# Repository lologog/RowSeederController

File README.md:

# DC Motor Controller for Row Seeder

## Project Description
This project focuses on the design and development of a modular DC motor controller system for a row seeder.
The system ensures precise control over seed dispensing and supports communication with external devices via CAN protocol.

The project consists of a main controller board an an extension board connected via 2.54mm pin sockets:
- **Main Controller Board**: Handles motor control, sensor readings and CAN communication protocol.
- **Extension Board**: Adds high-current switches and extra digital inputs for expanded functionality.

This modular approach allows future modifications for broader compatibility and functionality.

---

## Features
### Main Controller Board:
- **Microcontroller**: STM32L476RGT6 (low power, high-performance Cortex-M4).
- **DC Motor Control**: H-bridge driver with speed and direction regulation using PWM.
- **CAN Communication**: Communication interface enabled by an SN65HVD230 transceiver, operating with a default baud rate of 500 kbits/s.
- **Sensor Inputs**:
  - Analog inputs (12V) for angle sensors.
  - Encoder inputs (5V and 12V) for speed control.

### Extension Board:
- **Digital Input Expansion**: Additional pins for external sensors or signals.
- **High-current Switches**: Reliable control of external loads through robust switches.
- **Modular Connectivity**: Connects seamlessly to the main board via pin sockets.

---

## PCB Renderings
- **Main Controller Board**:

- **Extension Board**:

  *Extension PCB made by my friend :)*

---

## **Real-World Implementation**
Below are images of the actual hardware implementation:

- **Fully assembled main controller**:

- **Main controller connected with extension board**:

- **Whole controller packed in a cover with 4 connectors**:

---

## Results
- **PWM Motor Control**: Verified precise speed and direction control for the DC motor.
- **Sensor Readings**: Successfully processed analog inputs and encoders.
- **PID Algorithm**: Achieved stable motor speed with minimal overshoot and fast response.
  
  *Example motor angular velocity step response (fs = 10Hz)*
- **CAN Communication**: Reliable message transmission with external systems.
  
  *Sending analog reading of distance sensor via CAN bus*
  
---

## CAN Identifiers Documentation

The following table includes example CAN IDs and their corresponding actions. These IDs are meant as examples and should be adjusted to fit the needs of the target hardware and system.

| ID      | Function                | Parameters                     | Message Type    | Notes                                     |
|---------|-------------------------|--------------------------------|-----------------|-------------------------------------------|
| 0x01    | Ping                    | None                           | Response        | Sends a "ping" response                   |
| 0x02    | Turn LED ON             | None                           | Request         | Turns on the LED                          |
| 0x03    | Turn LED OFF            | None                           | Request         | Turns off the LED                         |
| 0x04    | Toggle LED state        | None                           | Request         | Toggles the LED state                     |
| 0x05    | Read distance sensor 1  | ADC channel                    | Request         | Reads analog measurement from channel 6   |
| 0x06    | Read distance sensor 2  | ADC channel                    | Request         | Reads analog measurement from channel 7   |
| 0x07    | Turn on/off switch 1    | 1 (ON), other (OFF)            | Request         | Controls power switch 1                   |
| 0x08    | Turn on/off switch 2    | 1 (ON), other (OFF)            | Request         | Controls power switch 2                   |
| 0x09    | Turn on/off switch 3    | 1 (ON), other (OFF)            | Request         | Controls power switch 3                   |
| 0x10    | Turn on/off switch 4    | 1 (ON), other (OFF)            | Request         | Controls power switch 4                   |
| 0x11    | Turn on/off switch 5    | 1 (ON), other (OFF)            | Request         | Controls power switch 5                   |
| 0x12    | Turn on/off switch 6    | 1 (ON), other (OFF)            | Request         | Controls power switch 6                   |
| 0x13    | Motor PID control       | RPM, direction                 | Request         | PID control for motor speed               |
| 0x14    | Stop motor              | None                           | Request         | Stops the motor                           |
| 0x15    | Motor percent control   | Percent, direction             | Request         | Controls motor using percentage duty cycle|

---

## Potential Improvements
- Support for a broader range of motors and sensors.
- Add more communication protocols and better diagnostic.
- Motor measurement for better motor control.
- Enhanced firmware for fault detection and recovery.
- Improved PID regulation using extrapolation between samples and implementation of angular speed control through current measurement.

## Author
- **Name**: Krzysztof Tomicki
- **Contact**: tomicki.krzysztof.pv@gmail.com

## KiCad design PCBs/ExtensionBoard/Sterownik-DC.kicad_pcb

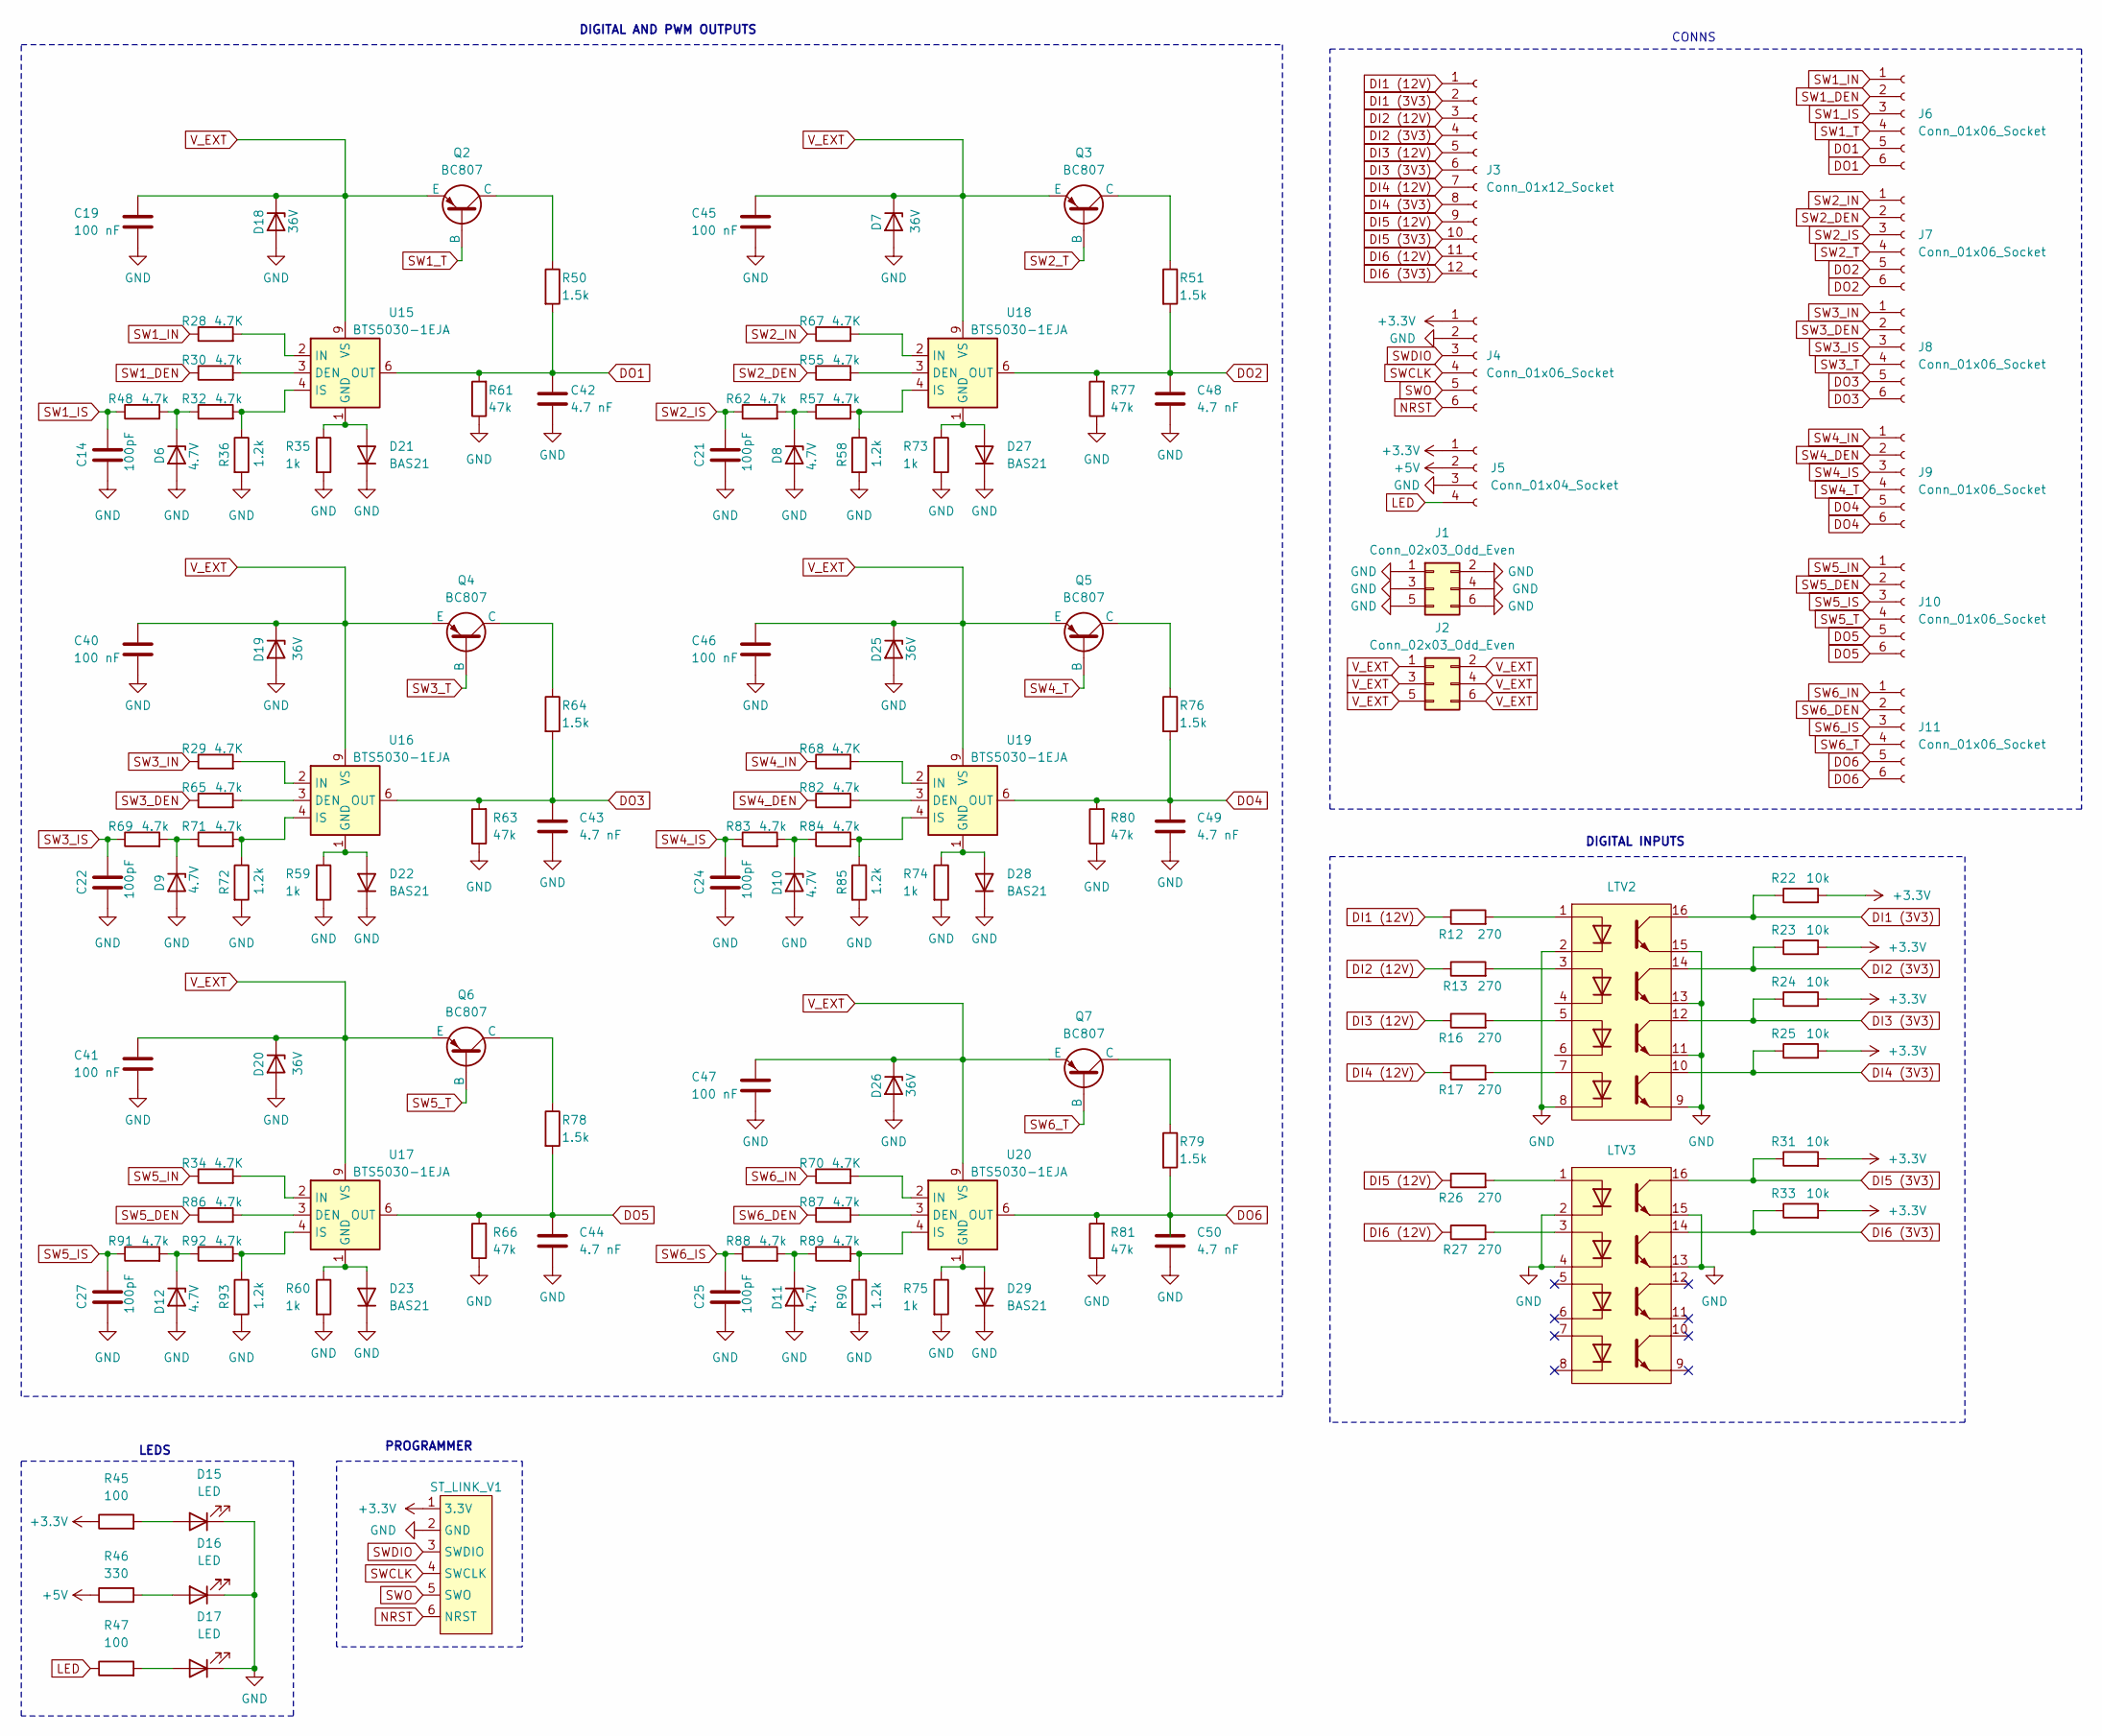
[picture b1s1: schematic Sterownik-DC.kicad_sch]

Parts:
C14, C21, C22, C24, C25, C27: 100pF; C_0805_2012Metric_Pad1.18x1.45mm_HandSolder
C19, C40, C41, C45, C46, C47: 100 nF; C_0805_2012Metric_Pad1.18x1.45mm_HandSolder
C42, C43, C44, C48, C49, C50: 4.7 nF; C_0805_2012Metric_Pad1.18x1.45mm_HandSolder
D6, D8, D9, D10, D11, D12: 4.7V; D_SOD-123
D7, D18, D19, D20, D25, D26: 36V; D_SOD-123
D15, D16, D17: LED; D_1206_3216Metric_Pad1.42x1.75mm_HandSolder
D21, D22, D23, D27, D28, D29: BAS21; SOT-23
J1, J2: Conn_02x03_Odd_Even; PinSocket_2x03_P2.54mm_Vertical
J3: Conn_01x12_Socket; PinSocket_2x06_P2.54mm_Vertical
J4, J6, J7, J8, J9, J10, J11: Conn_01x06_Socket; PinSocket_2x03_P2.54mm_Vertical
J5: Conn_01x04_Socket; PinSocket_2x02_P2.54mm_Vertical
LTV2, LTV3: DIP-16_W7.62mm
Q2, Q3, Q4, Q5, Q6, Q7: BC807; SOT-23-3
R12, R13, R16, R17, R26, R27: 270; R_1206_3216Metric_Pad1.30x1.75mm_HandSolder
R22, R23, R24, R25, R31, R33: 10k; R_0805_2012Metric_Pad1.20x1.40mm_HandSolder
R28, R29, R34, R67, R68, R70: 4.7K; R_0805_2012Metric_Pad1.20x1.40mm_HandSolder
R30, R32, R48, R55, R57, R62, R65, R69, R71, R82, R83, R84, R86, R87, R88, R89, R91, R92: 4.7k; R_0805_2012Metric_Pad1.20x1.40mm_HandSolder
R35, R59, R60, R73, R74, R75: 1k; R_0805_2012Metric_Pad1.20x1.40mm_HandSolder
R36, R58, R72, R85, R90, R93: 1.2k; R_0805_2012Metric_Pad1.20x1.40mm_HandSolder
R45, R47: 100; R_0805_2012Metric_Pad1.20x1.40mm_HandSolder
R46: 330; R_0805_2012Metric_Pad1.20x1.40mm_HandSolder
R50, R51, R64, R76, R78, R79: 1.5k; R_0805_2012Metric_Pad1.20x1.40mm_HandSolder
R61, R63, R66, R77, R80, R81: 47k; R_0805_2012Metric_Pad1.20x1.40mm_HandSolder
ST_LINK_V1: PinSocket_2x05_P2.54mm_Vertical
U15, U16, U17, U18, U19, U20: BTS5030-1EJA; Infineon_PG-DSO-8-43

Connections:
+3.3V: J4.1, J5.1, R22.2, R23.2, R24.2, R25.2, R31.2, R33.2, R45.1, ST_LINK_V1.1 (3.3V)
+5V: J5.2, R46.1
DI1 (3V3): J3.2, LTV2.16, R22.1
DI1 (12V): J3.1, R12.1
DI2 (3V3): J3.4, LTV2.14, R23.1
DI2 (12V): J3.3, R13.1
DI3 (3V3): J3.6, LTV2.12, R24.1
DI3 (12V): J3.5, R16.1
DI4 (3V3): J3.8, LTV2.10, R25.1
DI4 (12V): J3.7, R17.1
DI5 (3V3): J3.10, LTV3.16, R31.1
DI5 (12V): J3.9, R26.1
DI6 (3V3): J3.12, LTV3.14, R33.1
DI6 (12V): J3.11, R27.1
DO1: C42.1, J6.5, J6.6, R50.2, R61.2, U15.6 (OUT), U15.7 (OUT), U15.8 (OUT)
DO2: C48.1, J7.5, J7.6, R51.2, R77.2, U18.6 (OUT), U18.7 (OUT), U18.8 (OUT)
DO3: C43.1, J8.5, J8.6, R63.2, R64.2, U16.6 (OUT), U16.7 (OUT), U16.8 (OUT); also elsewhere on the board
DO4: C49.1, J9.5, J9.6, R76.2, R80.2, U19.6 (OUT), U19.7 (OUT), U19.8 (OUT)
DO5: C44.1, J10.5, J10.6, R66.2, R78.2, U17.6 (OUT), U17.7 (OUT), U17.8 (OUT)
DO6: C50.1, J11.5, J11.6, R79.2, R81.2, U20.6 (OUT), U20.7 (OUT), U20.8 (OUT)
GND: C14.1, C19.2, C21.1, C22.1, C24.1, C25.1, C27.1, C40.2, C41.2, C42.2, C43.2, C44.2, C45.2, C46.2, C47.2, C48.2, C49.2, C50.2, D6.2 (A), D7.2 (A), D8.2 (A), D9.2 (A), D10.2 (A), D12.2 (A), D15.1 (K), D16.1 (K), D17.1 (K), D18.2 (A), D19.2 (A), D20.2 (A), D21.3 (K), D22.3 (K), D23.3 (K), D25.2 (A), D26.2 (A), D27.3 (K), D28.3 (K), D29.3 (K), J1.1, J1.2, J1.3, J1.4, J1.5, J1.6, J4.2, J5.3, LTV2.2, LTV2.8, LTV2.9, LTV2.11, LTV2.13, LTV2.15, LTV3.2, LTV3.4, LTV3.13, LTV3.15, R35.2, R36.2, R58.2, R59.2, R60.2, R61.1, R63.1, R66.1, R72.2, R73.2, R74.2, R75.2, R77.1, R80.1, R81.1, R85.2, R90.2, R93.2, ST_LINK_V1.2 (GND); also elsewhere on the board
LED: J5.4, R47.1
NRST: J4.6, ST_LINK_V1.6 (NRST)
unnamed: D6.1 (K), R32.1, R48.2
unnamed: D8.1 (K), R57.1, R62.2
unnamed: D9.1 (K), R69.2, R71.1
unnamed: D10.1 (K), R83.2, R84.1
unnamed 27: D11.1 (K), R88.2, R89.1; also elsewhere on the board
unnamed: D12.1 (K), R91.2, R92.1
unnamed: D15.2 (A), R45.2
unnamed: D16.2 (A), R46.2
unnamed: D17.2 (A), R47.2
unnamed: D21.1 (A), R35.1, U15.1 (GND)
unnamed: D22.1 (A), R59.1, U16.1 (GND)
unnamed: D23.1 (A), R60.1, U17.1 (GND)
unnamed: D27.1 (A), R73.1, U18.1 (GND)
unnamed: D28.1 (A), R74.1, U19.1 (GND)
unnamed: D29.1 (A), R75.1, U20.1 (GND)
unnamed: LTV2.1, R12.2
unnamed: LTV2.3, R13.2
unnamed: LTV2.5, R16.2
unnamed: LTV2.7, R17.2
unnamed: LTV3.1, R26.2
unnamed: LTV3.3, R27.2
unnamed: Q2.1 (C), R50.1
unnamed: Q3.1 (C), R51.1
unnamed 46: Q4.1 (C), R64.1; also elsewhere on the board
unnamed: Q5.1 (C), R76.1
unnamed: Q6.1 (C), R78.1
unnamed: Q7.1 (C), R79.1
unnamed: R30.2, U15.3 (DEN)
unnamed: R28.2, U15.2 (IN)
unnamed: R32.2, R36.1, U15.4 (IS)
unnamed: R65.2, U16.3 (DEN)
unnamed: R29.2, U16.2 (IN)
unnamed: R71.2, R72.1, U16.4 (IS)
unnamed: R86.2, U17.3 (DEN)
unnamed: R34.2, U17.2 (IN)
unnamed: R92.2, R93.1, U17.4 (IS)
unnamed: R55.2, U18.3 (DEN)
unnamed: R67.2, U18.2 (IN)
unnamed: R57.2, R58.1, U18.4 (IS)
unnamed: R82.2, U19.3 (DEN)
unnamed: R68.2, U19.2 (IN)
unnamed: R84.2, R85.1, U19.4 (IS)
unnamed: R87.2, U20.3 (DEN)
unnamed: R70.2, U20.2 (IN)
unnamed: R89.2, R90.1, U20.4 (IS)
SW1_DEN: J6.2, R30.1
SW1_IN: J6.1, R28.1
SW1_IS: C14.2, J6.3, R48.1
SW1_T: J6.4, Q2.2 (B)
SW2_DEN: J7.2, R55.1
SW2_IN: J7.1, R67.1
SW2_IS: C21.2, J7.3, R62.1
SW2_T: J7.4, Q3.2 (B)
SW3_DEN: J8.2, R65.1
SW3_IN: J8.1, R29.1
SW3_IS: C22.2, J8.3, R69.1
SW3_T: J8.4, Q4.2 (B)
SW4_DEN: J9.2, R82.1
SW4_IN: J9.1, R68.1
SW4_IS: C24.2, J9.3, R83.1
SW4_T: J9.4, Q5.2 (B)
SW5_DEN: J10.2, R86.1
SW5_IN: J10.1, R34.1
SW5_IS: C27.2, J10.3, R91.1
SW5_T: J10.4, Q6.2 (B)
SW6_DEN: J11.2, R87.1
SW6_IN: J11.1, R70.1
SW6_IS: C25.2, J11.3, R88.1
SW6_T: J11.4, Q7.2 (B)
SWCLK: J4.4, ST_LINK_V1.4 (SWCLK)
SWDIO: J4.3, ST_LINK_V1.3 (SWDIO)
SWO: J4.5, ST_LINK_V1.5 (SWO)
V_EXT: C19.1, C40.1, C41.1, C45.1, C46.1, C47.1, D7.1 (K), D18.1 (K), D19.1 (K), D20.1 (K), D25.1 (K), D26.1 (K), J2.1, J2.2, J2.3, J2.4, J2.5, J2.6, Q2.3 (E), Q3.3 (E), Q4.3 (E), Q5.3 (E), Q6.3 (E), Q7.3 (E), U15.9 (VS), U16.9 (VS), U17.9 (VS), U18.9 (VS), U19.9 (VS), U20.9 (VS)

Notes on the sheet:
CONNS
DIGITAL INPUTS
DIGITAL AND PWM OUTPUTS
LEDS
PROGRAMMER

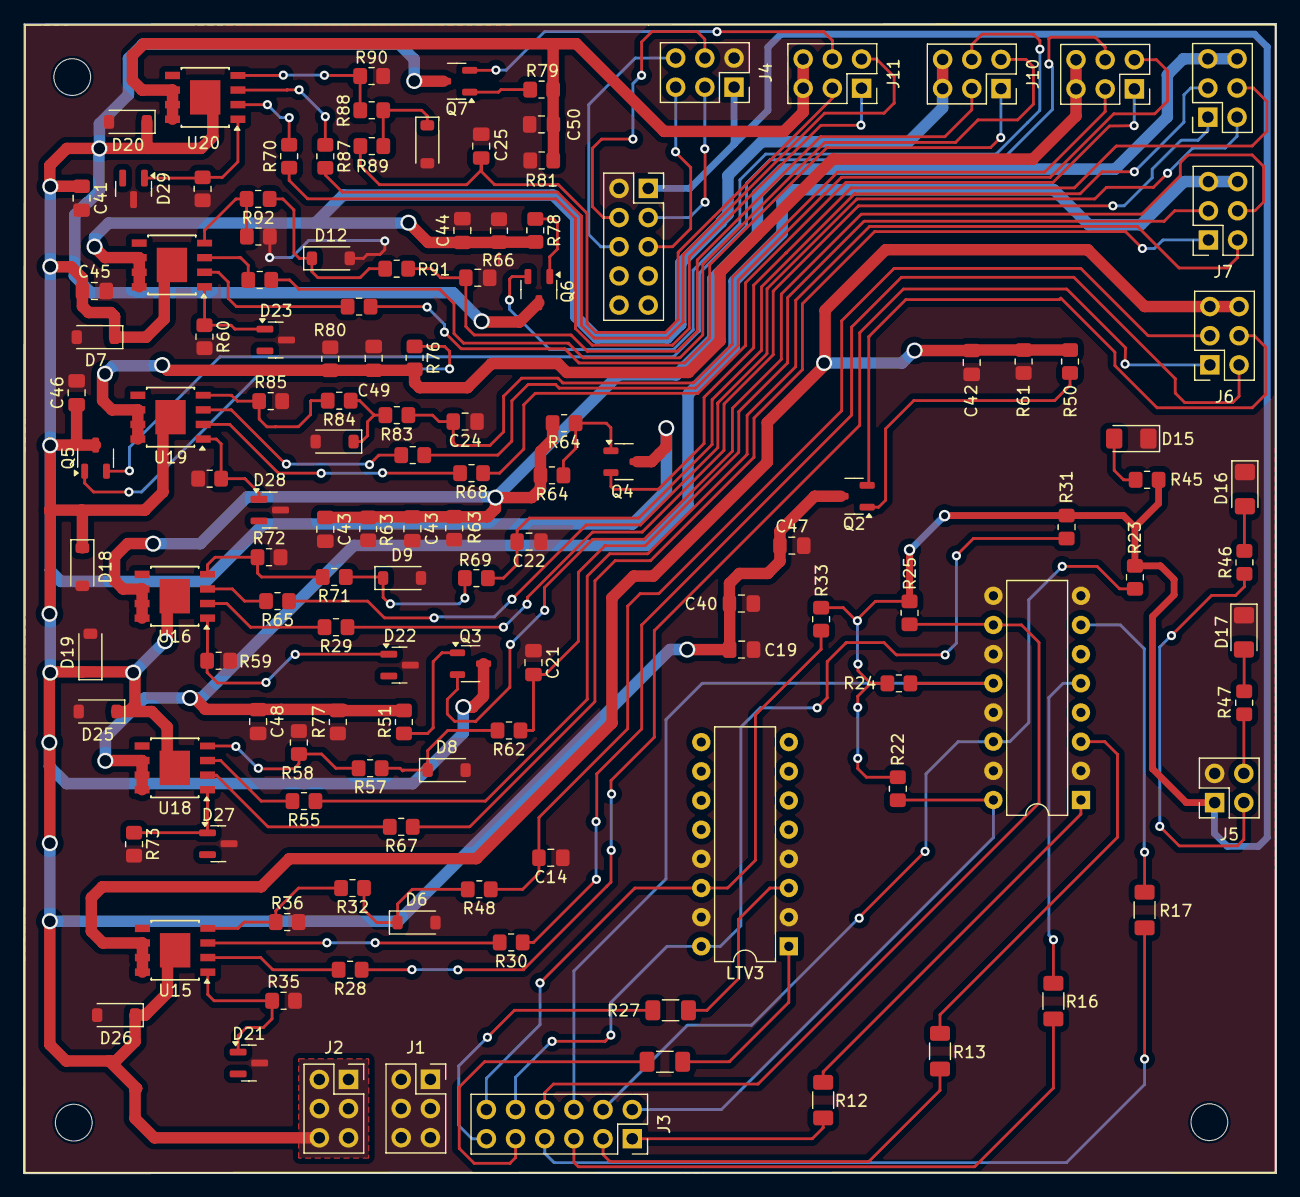
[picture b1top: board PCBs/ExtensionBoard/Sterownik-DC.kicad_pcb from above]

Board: 2 copper layers, 109.1 x 100.1 mm, 131 parts (0 on the bottom side), 96 nets.

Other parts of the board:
C25#2: 4.7V; D_SOD-123
C43#2: 4.7 nF; C_0805_2012Metric_Pad1.18x1.45mm_HandSolder
R63#2: 47k; R_0805_2012Metric_Pad1.20x1.40mm_HandSolder
R64#2: 1.5k; R_0805_2012Metric_Pad1.20x1.40mm_HandSolder

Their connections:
DO3: C43#2.1, R63#2.2, R64#2.2; also elsewhere on the board
GND: C25#2.2 (A), C43#2.2, R63#2.1; also elsewhere on the board
unnamed 27: C25#2.1 (K); also elsewhere on the board
unnamed 46: R64#2.1; also elsewhere on the board

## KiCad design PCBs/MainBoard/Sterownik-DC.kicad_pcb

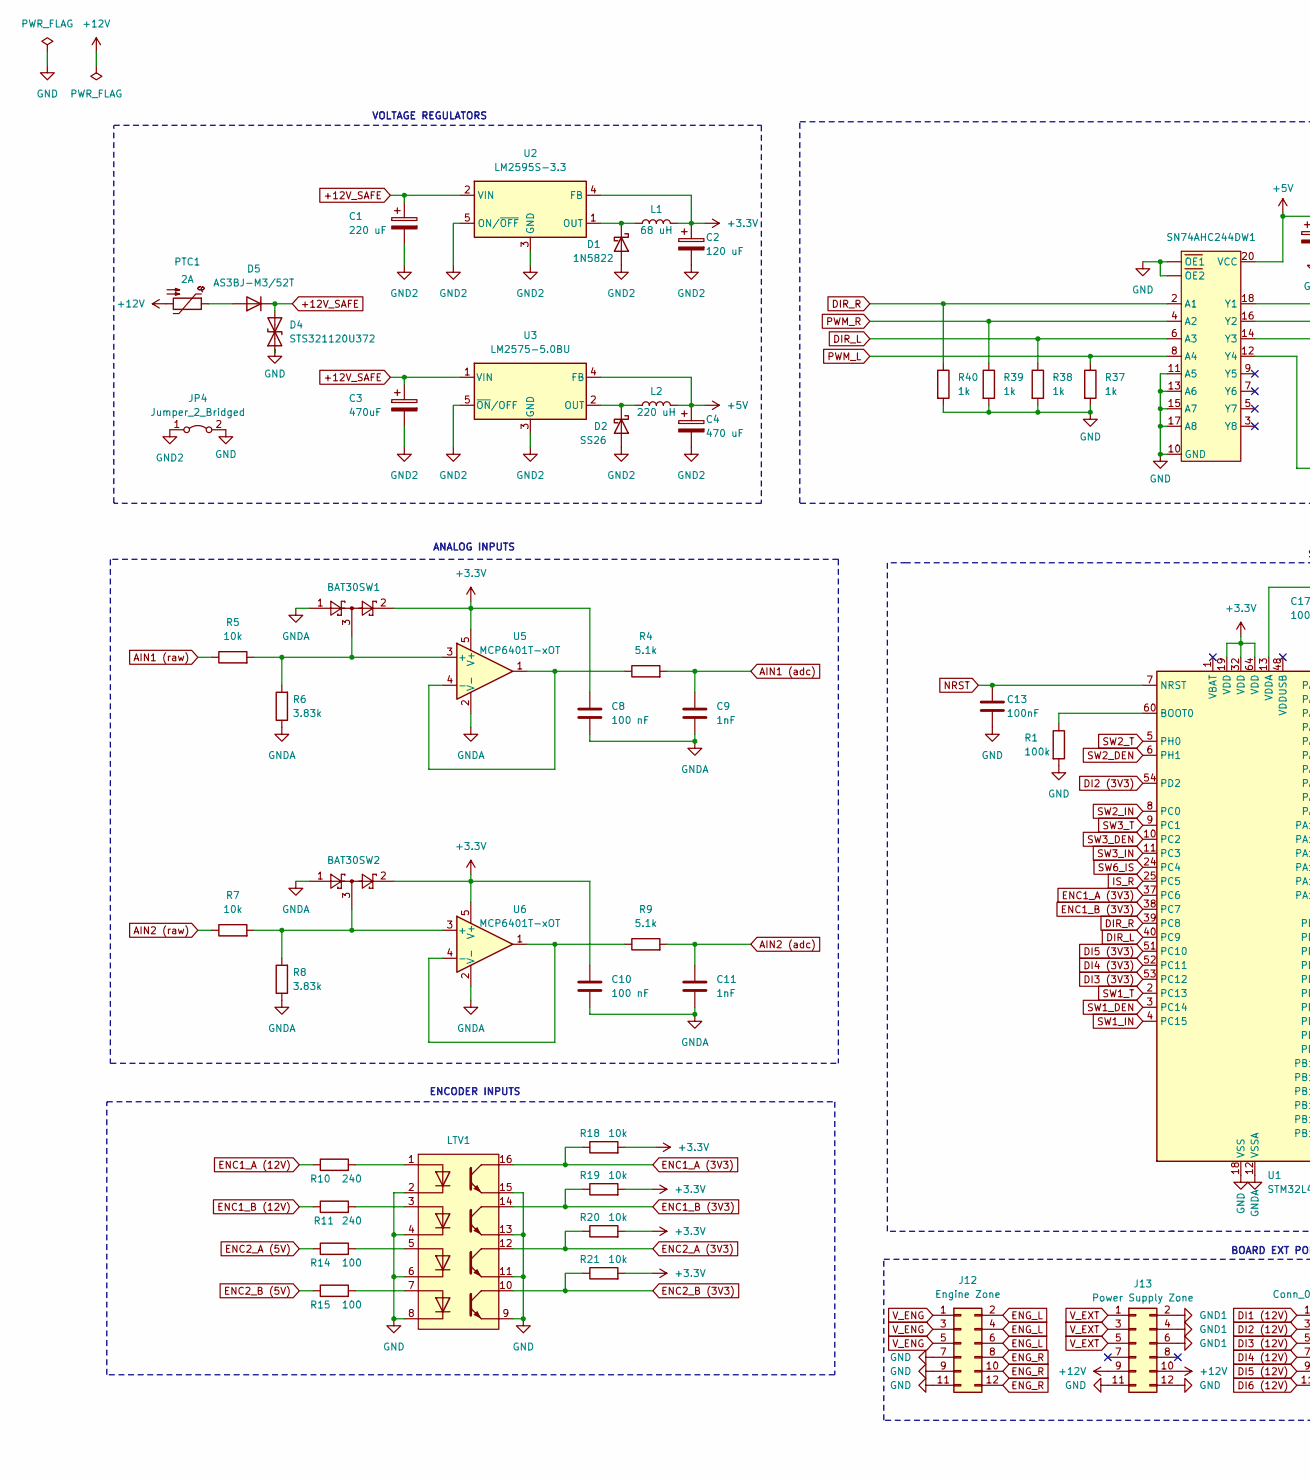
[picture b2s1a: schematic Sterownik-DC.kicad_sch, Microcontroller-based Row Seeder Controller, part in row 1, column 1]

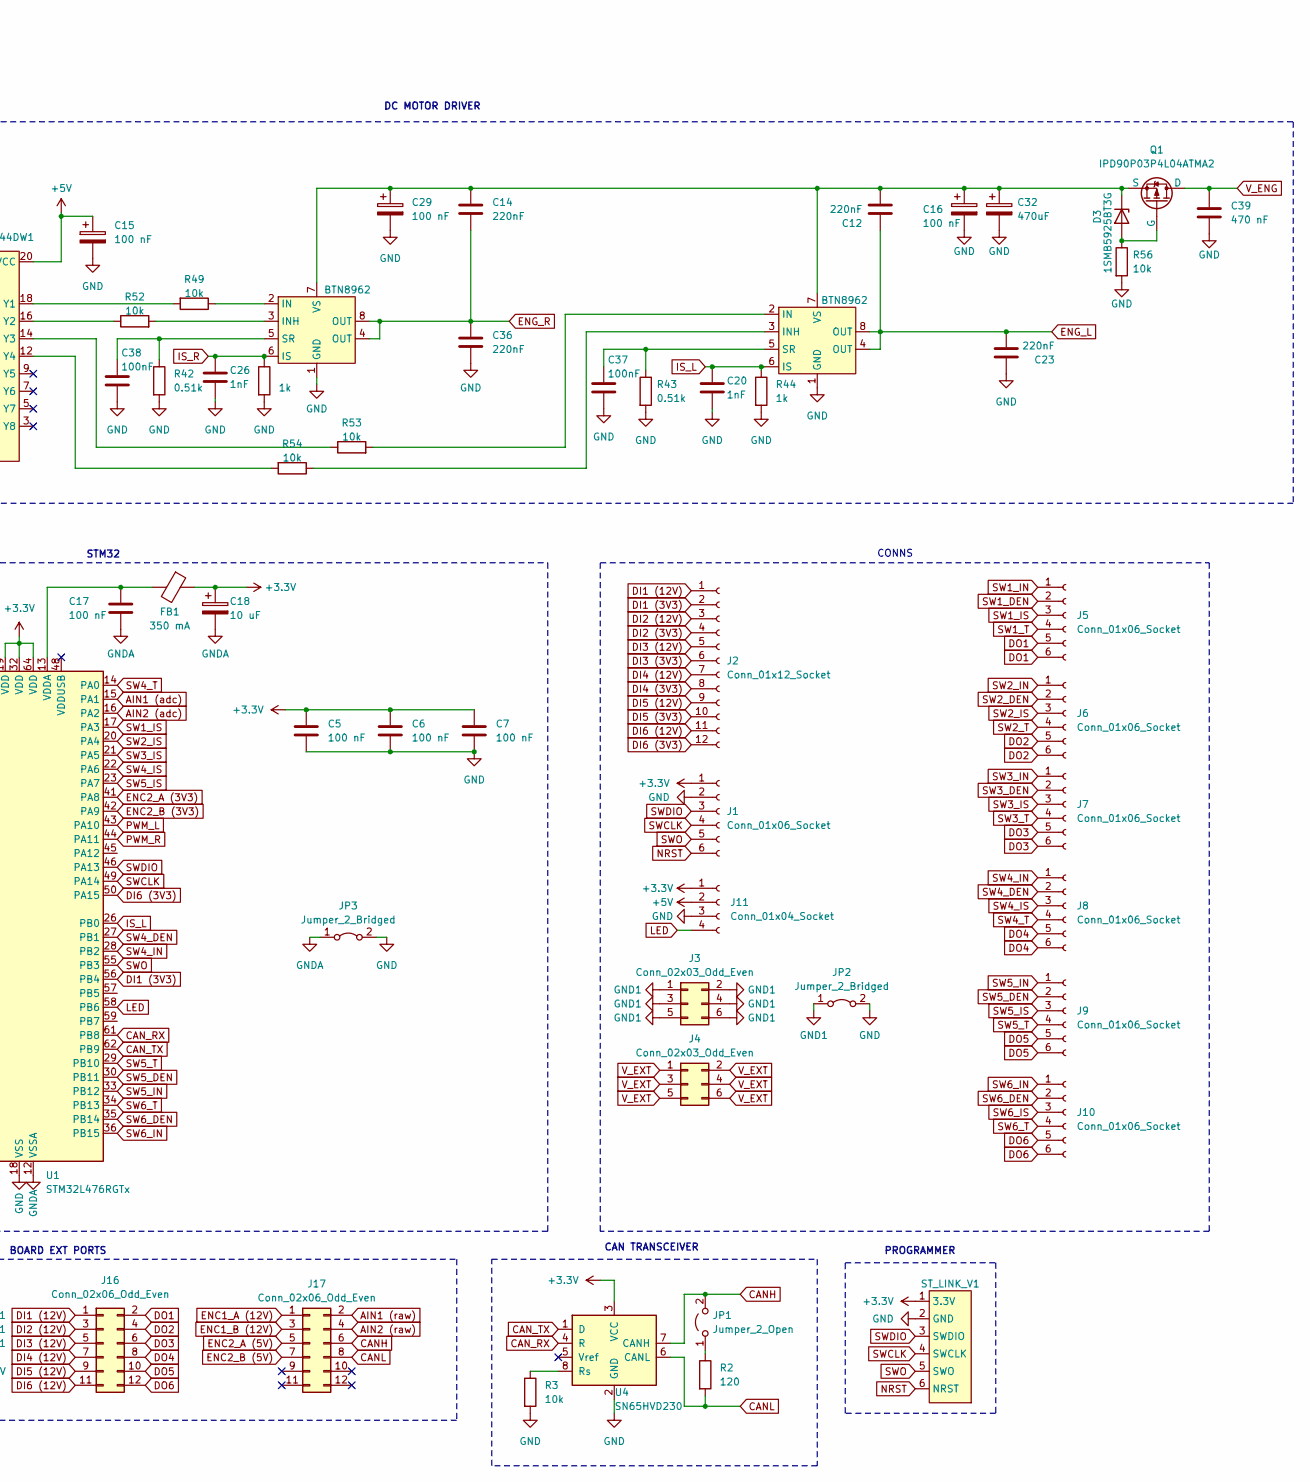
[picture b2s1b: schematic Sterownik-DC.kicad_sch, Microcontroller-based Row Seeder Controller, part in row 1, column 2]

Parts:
BAT30SW1, BAT30SW2: SOT-323_SC-70
C1: 220 uF; CP_Radial_D8.0mm_P3.50mm
C2: 120 uF; CP_Radial_D8.0mm_P3.50mm
C3, C32: 470uF; CP_Radial_D10.0mm_P5.00mm
C4: 470 uF; CP_Radial_D10.0mm_P5.00mm
C5, C6, C7, C8, C10, C15, C16, C17, C29: 100 nF; C_0805_2012Metric_Pad1.18x1.45mm_HandSolder
C9, C11, C20, C26: 1nF; C_0805_2012Metric_Pad1.18x1.45mm_HandSolder
C12, C14, C23, C36: 220nF; C_0805_2012Metric_Pad1.18x1.45mm_HandSolder
C13, C37, C38: 100nF; C_0805_2012Metric_Pad1.18x1.45mm_HandSolder
C18: 10 uF; C_0805_2012Metric_Pad1.18x1.45mm_HandSolder
C39: 470 nF; C_0805_2012Metric_Pad1.18x1.45mm_HandSolder
D1: 1N5822; D_SMA_Handsoldering
D2: SS26; Zener_diode_DO-214AA
D3: 1SMB5925BT3G; 1SMB5913BT3
D4: STS321120U372; D_SOD-323_HandSoldering
D5: AS3BJ-M3/52T; AS3BJ-M3-52T
FB1: 350 mA; L_1206_3216Metric_Pad1.22x1.90mm_HandSolder
J1, J5, J6, J7, J8, J9, J10: Conn_01x06_Socket; PinSocket_2x03_P2.54mm_Vertical
J2: Conn_01x12_Socket; PinSocket_2x06_P2.54mm_Vertical
J3, J4: Conn_02x03_Odd_Even; PinSocket_2x03_P2.54mm_Vertical
J11: Conn_01x04_Socket; PinSocket_2x02_P2.54mm_Vertical
J12: Engine Zone; BIG_CONN
J13: Power Supply Zone; BIG_CONN
J16, J17: Conn_02x06_Odd_Even; BIG_CONN
JP1: Jumper_2_Open; PinHeader_1x02_P2.54mm_Vertical
JP2, JP3, JP4: Jumper_2_Bridged; SolderJumper-2_P1.3mm_Bridged2Bar_Pad1.0x1.5mm
L1: 68 uH; SRR1280
L2: 220 uH; MSS1246T
LTV1: DIP-16_W7.62mm
PTC1: 2A; 0ZCF Series
Q1: IPD90P03P4L04ATMA2; TO-252-3_TabPin2
R1: 100k; R_0805_2012Metric_Pad1.20x1.40mm_HandSolder
R2: 120; R_0805_2012Metric_Pad1.20x1.40mm_HandSolder
R3, R5, R7, R18, R19, R20, R21, R49, R52, R53, R54, R56: 10k; R_0805_2012Metric_Pad1.20x1.40mm_HandSolder
R4, R9: 5.1k; R_0805_2012Metric_Pad1.20x1.40mm_HandSolder
R6, R8: 3.83k; R_0805_2012Metric_Pad1.20x1.40mm_HandSolder
R10, R11: 240; R_2512_6332Metric_Pad1.40x3.35mm_HandSolder
R14, R15: 100; R_0805_2012Metric_Pad1.20x1.40mm_HandSolder
R37, R38, R39, R40, R41, R44: 1k; R_0805_2012Metric_Pad1.20x1.40mm_HandSolder
R42, R43: 0.51k; R_0805_2012Metric_Pad1.20x1.40mm_HandSolder
SN74AHC244DW1: SOIC-20W_7.5x12.8mm_P1.27mm
ST_LINK_V1: PinSocket_2x05_P2.54mm_Vertical
U1: STM32L476RGTx; LQFP-64_10x10mm_P0.5mm
U2: LM2595S-3.3; TO-263-5_TabPin3
U3: LM2575-5.0BU; TO-263-5_TabPin3
U4: SN65HVD230; SOIC-8_3.9x4.9mm_P1.27mm
U5, U6: MCP6401T-xOT; SOT-23-5
U8, U9: BTN8962; TO-263-7_TabPin8

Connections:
+3.3V: BAT30SW1.2, BAT30SW2.2, C2.1, C5.1, C6.1, C7.1, C8.1, C10.1, C18.1, FB1.1, J1.1, J11.1, L1.2, R18.2, R19.2, R20.2, R21.2, ST_LINK_V1.1 (3.3V), U1.19 (VDD), U1.32 (VDD), U1.64 (VDD), U2.4 (FB), U4.3 (VCC), U5.5 (V+), U6.5 (V+)
+5V: C4.1, C15.1, J11.2, L2.2, SN74AHC244DW1.20 (VCC), U3.4 (FB)
+12V: J13.9, J13.10, PTC1.2
+12V_SAFE: C1.1, C3.1, D4.2 (A2), D5.1 (K), U2.2 (VIN), U3.1 (VIN)
AIN1 (adc): C9.1, R4.2, U1.15 (PA1)
AIN1 (raw): J17.2, R5.1
AIN2 (adc): C11.1, R9.2, U1.16 (PA2)
AIN2 (raw): J17.4, R7.1
CANH: J17.6, JP1.2 (B), U4.7 (CANH)
CANL: J17.8, R2.2, U4.6 (CANL)
CAN_RX: U1.61 (PB8), U4.4 (R)
CAN_TX: U1.62 (PB9), U4.1 (D)
DI1 (3V3): J2.2, U1.56 (PB4)
DI1 (12V): J2.1, J16.1
DI2 (3V3): J2.4, U1.54 (PD2)
DI2 (12V): J2.3, J16.3
DI3 (3V3): J2.6, U1.53 (PC12)
DI3 (12V): J2.5, J16.5
DI4 (3V3): J2.8, U1.52 (PC11)
DI4 (12V): J2.7, J16.7
DI5 (3V3): J2.10, U1.51 (PC10)
DI5 (12V): J2.9, J16.9
DI6 (3V3): J2.12, U1.50 (PA15)
DI6 (12V): J2.11, J16.11
DIR_L: R38.1, SN74AHC244DW1.6 (A3), U1.40 (PC9)
DIR_R: R40.1, SN74AHC244DW1.2 (A1), U1.39 (PC8)
DO1: J5.5, J5.6, J16.2
DO2: J6.5, J6.6, J16.4
DO3: J7.5, J7.6, J16.6
DO4: J8.5, J8.6, J16.8
DO5: J9.5, J9.6, J16.10
DO6: J10.5, J10.6, J16.12
ENC1_A (3V3): LTV1.16, R18.1, U1.37 (PC6)
ENC1_A (12V): J17.1, R10.1
ENC1_B (3V3): LTV1.14, R19.1, U1.38 (PC7)
ENC1_B (12V): J17.3, R11.1
ENC2_A (3V3): LTV1.12, R20.1, U1.41 (PA8)
ENC2_A (5V): J17.5, R14.1
ENC2_B (3V3): LTV1.10, R21.1, U1.42 (PA9)
ENC2_B (5V): J17.7, R15.1
ENG_L: C12.1, C23.2, J12.2, J12.4, J12.6, U9.4 (OUT), U9.8 (OUT)
ENG_R: C14.2, C36.1, J12.8, J12.10, J12.12, U8.4 (OUT), U8.8 (OUT)
GND: C5.2, C6.2, C7.2, C13.2, C15.2, C16.2, C20.2, C23.1, C26.2, C29.2, C32.2, C36.2, C37.2, C38.2, C39.2, D4.1 (A1), J1.2, J11.3, J12.7, J12.9, J12.11, J13.11, J13.12, JP2.2 (B), JP3.2 (B), JP4.2 (B), LTV1.2, LTV1.4, LTV1.6, LTV1.8, LTV1.9, LTV1.11, LTV1.13, LTV1.15, R1.2, R3.2, R37.2, R38.2, R39.2, R40.2, R41.2, R42.2, R43.2, R44.2, R56.2, SN74AHC244DW1. (OE1), SN74AHC244DW1.1 (OE1), SN74AHC244DW1.10 (GND), SN74AHC244DW1.11 (A5), SN74AHC244DW1.13 (A6), SN74AHC244DW1.15 (A7), SN74AHC244DW1.17 (A8), SN74AHC244DW1.19 (OE2), ST_LINK_V1.2 (GND), U1.18 (VSS), U1.31 (VSS), U1.47 (VSS), U1.63 (VSS), U4.2 (GND), U8.1 (GND), U9.1 (GND)
GND1: J3.1, J3.2, J3.3, J3.4, J3.5, J3.6, J13.2, J13.4, J13.6, JP2.1 (A)
GND2: C1.2, C2.2, C3.2, C4.2, D1.2 (A), D2.2 (A), JP4.1 (A), U2.3 (GND), U2.5 (ON/~OFF), U3.3 (GND), U3.5 (~ON/OFF)
GNDA: BAT30SW1.1, BAT30SW2.1, C8.2, C9.2, C10.2, C11.2, C17.2, C18.2, JP3.1 (A), R6.1, R8.1, U1.12 (VSSA), U5.2 (V-), U6.2 (V-)
IS_L: C20.1, R44.1, U1.26 (PB0), U9.6 (IS)
IS_R: C26.1, R41.1, U1.25 (PC5), U8.6 (IS)
LED: J11.4, U1.58 (PB6)
NRST: C13.1, J1.6, ST_LINK_V1.6 (NRST), U1.7 (NRST)
unnamed: D1.1 (K), L1.1, U2.1 (OUT)
unnamed: D2.1 (K), L2.1, U3.2 (OUT)
unnamed: D3.2 (A), Q1.1 (G), R56.1
unnamed: C12.2, C14.1, C16.1, C29.1, C32.1, D3.1 (K), Q1.3 (S), U8.7 (VS), U9.7 (VS)
unnamed: D5.2 (A), PTC1.1
unnamed: JP1.1 (A), R2.1
unnamed: LTV1.1, R10.2
unnamed: LTV1.3, R11.2
unnamed: LTV1.5, R14.2
unnamed: LTV1.7, R15.2
unnamed: R49.2, SN74AHC244DW1.18 (Y1)
unnamed: R52.1, SN74AHC244DW1.16 (Y2)
unnamed: R53.1, SN74AHC244DW1.14 (Y3)
unnamed: R54.2, SN74AHC244DW1.12 (Y4)
unnamed: R1.1, U1.60 (BOOT0)
unnamed: C17.1, FB1.2, U1.13 (VDDA)
unnamed: R3.1, U4.8 (Rs)
unnamed: BAT30SW1.3, R5.2, R6.2, U5.3 (+)
unnamed: R4.1, U5.1, U5.4 (-)
unnamed: BAT30SW2.3, R7.2, R8.2, U6.3 (+)
unnamed: R9.1, U6.1, U6.4 (-)
unnamed: R49.1, U8.2 (IN)
unnamed: R52.2, U8.3 (INH)
unnamed: C38.1, R42.1, U8.5 (SR)
unnamed: R53.2, U9.2 (IN)
unnamed: R54.1, U9.3 (INH)
unnamed: C37.1, R43.1, U9.5 (SR)
PWM_L: R37.1, SN74AHC244DW1.8 (A4), U1.43 (PA10)
PWM_R: R39.1, SN74AHC244DW1.4 (A2), U1.44 (PA11)
SW1_DEN: J5.2, U1.3 (PC14)
SW1_IN: J5.1, U1.4 (PC15)
SW1_IS: J5.3, U1.17 (PA3)
SW1_T: J5.4, U1.2 (PC13)
SW2_DEN: J6.2, U1.6 (PH1)
SW2_IN: J6.1, U1.8 (PC0)
SW2_IS: J6.3, U1.20 (PA4)
SW2_T: J6.4, U1.5 (PH0)
SW3_DEN: J7.2, U1.10 (PC2)
SW3_IN: J7.1, U1.11 (PC3)
SW3_IS: J7.3, U1.21 (PA5)
SW3_T: J7.4, U1.9 (PC1)
SW4_DEN: J8.2, U1.27 (PB1)
SW4_IN: J8.1, U1.28 (PB2)
SW4_IS: J8.3, U1.22 (PA6)
SW4_T: J8.4, U1.14 (PA0)
SW5_DEN: J9.2, U1.30 (PB11)
SW5_IN: J9.1, U1.33 (PB12)
SW5_IS: J9.3, U1.23 (PA7)
SW5_T: J9.4, U1.29 (PB10)
SW6_DEN: J10.2, U1.35 (PB14)
SW6_IN: J10.1, U1.36 (PB15)
SW6_IS: J10.3, U1.24 (PC4)
SW6_T: J10.4, U1.34 (PB13)
SWCLK: J1.4, ST_LINK_V1.4 (SWCLK), U1.49 (PA14)
SWDIO: J1.3, ST_LINK_V1.3 (SWDIO), U1.46 (PA13)
SWO: J1.5, ST_LINK_V1.5 (SWO), U1.55 (PB3)
V_ENG: C39.1, J12.1, J12.3, J12.5, Q1.2 (D)
V_EXT: J4.1, J4.2, J4.3, J4.4, J4.5, J4.6, J13.1, J13.3, J13.5

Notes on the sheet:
DC MOTOR DRIVER
CONNS
PROGRAMMER
CAN TRANSCEIVER
ANALOG INPUTS
BOARD EXT PORTS
ENCODER INPUTS
STM32
VOLTAGE REGULATORS

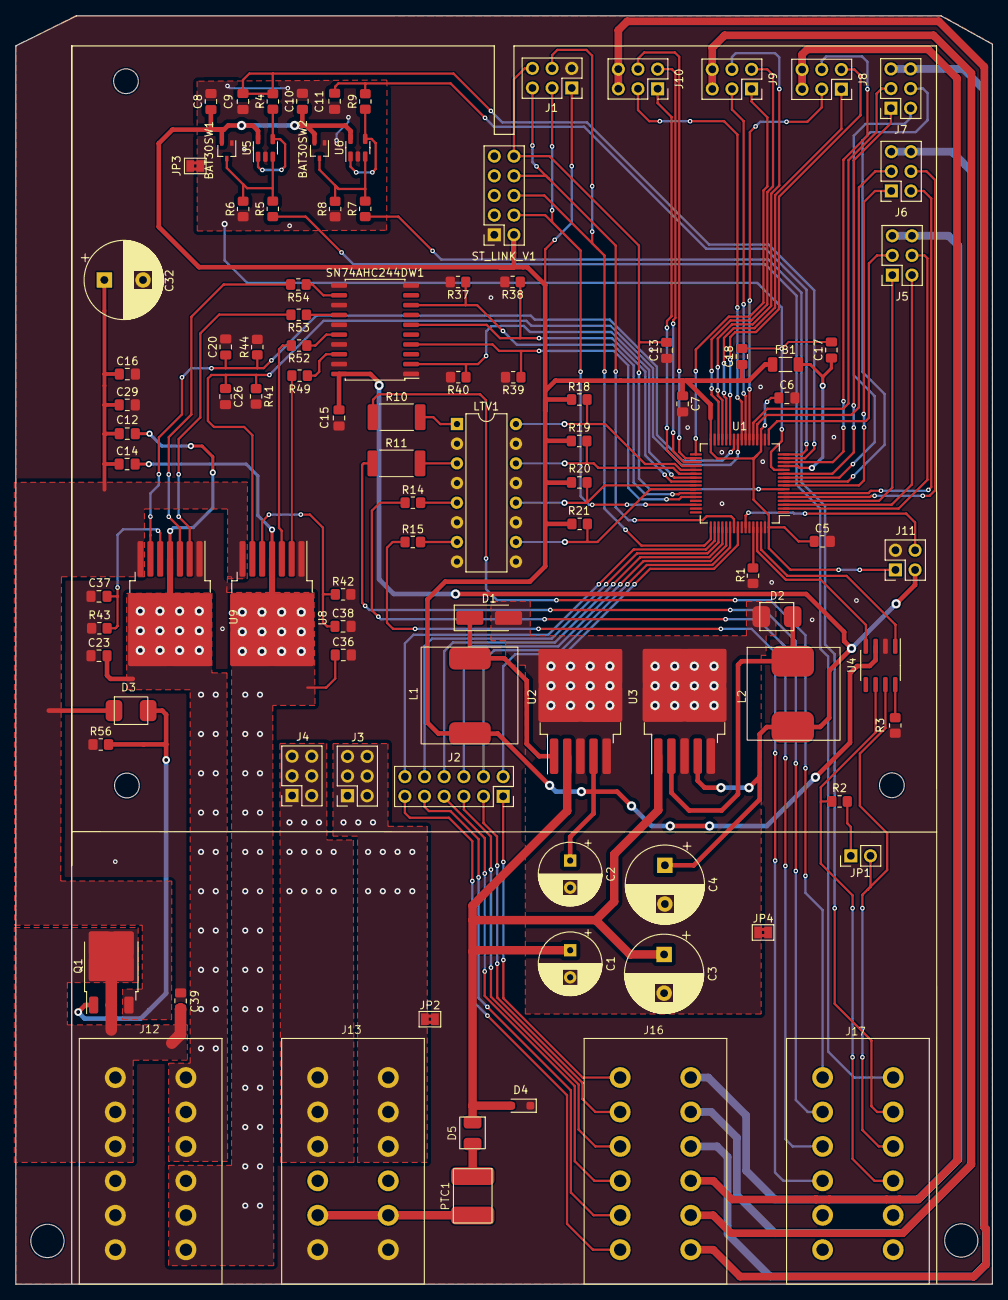
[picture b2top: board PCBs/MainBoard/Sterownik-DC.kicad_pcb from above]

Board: 2 copper layers, 126.2 x 163.9 mm, 99 parts (0 on the bottom side), 108 nets.

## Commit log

2025-01-09 project: add project files
2025-01-09 project: add bin and hex files
2025-01-09 project: add digital pins
2025-01-09 project: add distance sensor pins and resolve clock issues
2025-01-09 project: add engine control pins and change HCLK frequency to 80 MHz
2025-01-09 project: add motor control files
2025-01-09 project: add motor init and motor percent control function
2025-01-09 project: add Motor_Stop function and solved problem with negative velocity input
2025-01-09 project: short but important comment
2025-01-09 project: configure encoder pins
2025-01-09 project: add 2 new files led.c and led.h with basic functions
2025-01-09 project: add toggle and blink with interval functions to led files
2025-01-09 project: one macro added to led.c
2025-01-10 project: add 2 new files encoder.c and encoder.h with init function, small corrections with #include main.h
2025-01-10 project: successful test of sending data from controler via CAN
2025-01-13 project: make encoder enum names more clear for the user by adding voltage in names
2025-01-13 project: add can.c, can.h, CAN initialisation and CAN send data functions
2025-01-13 project: prototype of filter configuring function
2025-01-13 project: working CAN bus with working filtering
2025-01-13 project: small correct in comment
2025-01-13 project: correction in calling encoder init functions
2025-01-13 project: turn on timer to help calculacte RPM
2025-01-13 project: clearing files for better work with encoder
2025-01-13 project: test of sending informations via CAN once a second for encoder purposes
2025-01-14 project: correctly getting impulses from encoder once a second
2025-01-14 project: calculating scaled RPM is working correctly
2025-01-14 project: configuring Encoder RPM function to handle 5 and 12V encoders
2025-01-14 project: refactoring RPM encoder function to make the code more readible
2025-01-14 project: remove necessary comments
2025-01-14 project: changing RPM freq to 10Hz
2025-01-16 project: add PID regulation in main.c function
2025-01-16 project: working PID control function in motor files
2025-01-16 project: small comment in motor.c
2025-01-16 project: working analog input value receiving
2025-01-16 project: setup of peripheral pins to control high current switches on second board and also pins to measure current from motor half bridges
2025-01-16 project: function to switch on/off diagnostic of power switches
2025-01-17 project: add can_logic files to handle main loop with flags logic
2025-01-17 project: working ping in controllers logic
2025-01-17 project: add basic CAN Id based commands and remove led_blink function
2025-01-17 project: motor control via CAN
2025-01-17 project: add motor percent control via CAN
2025-01-17 Add PID motor control graph
2025-01-17 Add CAN screen
2025-01-18 Add table to readme
2025-01-18 Baud rate update in readme
2025-01-18 Change bits to kbits
2025-01-19 one more potential improvement
2025-01-20 project: bugfix with only turning on power switches - now it also turns off
2025-01-20 project: deliting repo that was cloned by mistake
2025-01-20 project: update readme for new power switches code
2025-01-20 one more switches update for readme
2025-01-20 project: final files arrangement
2025-01-20 project: correction in files
2025-01-30 project: add lower board in final state
2025-01-30 project: add upper board in final state
2025-01-30 project: add board in cover
2025-01-30 project: add real world photos in readme
2025-01-30 project: add names on real world photos
2025-03-07 README: Add new 3D render of the main board
2025-03-07 README: add new photo to README
2025-03-09 Project: add Main PCB project
2025-03-16 Project: add Extension Board PCB files
2025-03-16 Project: add ICs 3D models to the extension board render image
2025-11-02 Add MIT License to the project
